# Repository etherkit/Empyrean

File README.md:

# Empyrean

### Installing Empyrean Support in Arduino IDE

1. Open the Arduino IDE and then navigate to the Preferences screen by selecting the ```File``` menu, and then ```Preferences```. Click the small button to the right of the text box labeled ```Additional Boards Manager URLs```, and then paste the following URL into the windows which pops up:
[https://github.com/etherkit/ArduinoBoards/raw/master/package_etherkit_index.json](https://github.com/etherkit/ArduinoBoards/raw/master/package_etherkit_index.json)
<br>Click OK to close this window, and then OK to close the Preferences.
2. Navigate to the Arduino Boards Manager in the IDE by selecting the ```Tools``` menu, then ```Board```, and then ```Boards Manager...```. In the search box in the upper right of the Boards Manager windows, type ```SAMD```.
3. In the search results list below, find the entry for ```Arduino SAMD Boards```, select it with your mouse, and then click the install button.
4. Next, find the entry for ```Etherkit SAMD Boards```, select it, and click the install button. Close the Boards Manager window when this is complete.
5. In the ```Tools > Boards``` menu, you should now see Empyrean Alpha and Empyrean Beta listed as board options. Select the appropriate board in order to start uploading sketches to your Empyrean.

### USB-UART (CDC) and Other Serial
You can access the built-in USB-UART (virtual serial port) by using the ```SerialUSB``` object in your sketch, just as you use ```Serial``` in AVR-powered Arduinos. You can also use pins 0 and 1 of Empyrean as a hardware serial port with the ```Serial1``` object.

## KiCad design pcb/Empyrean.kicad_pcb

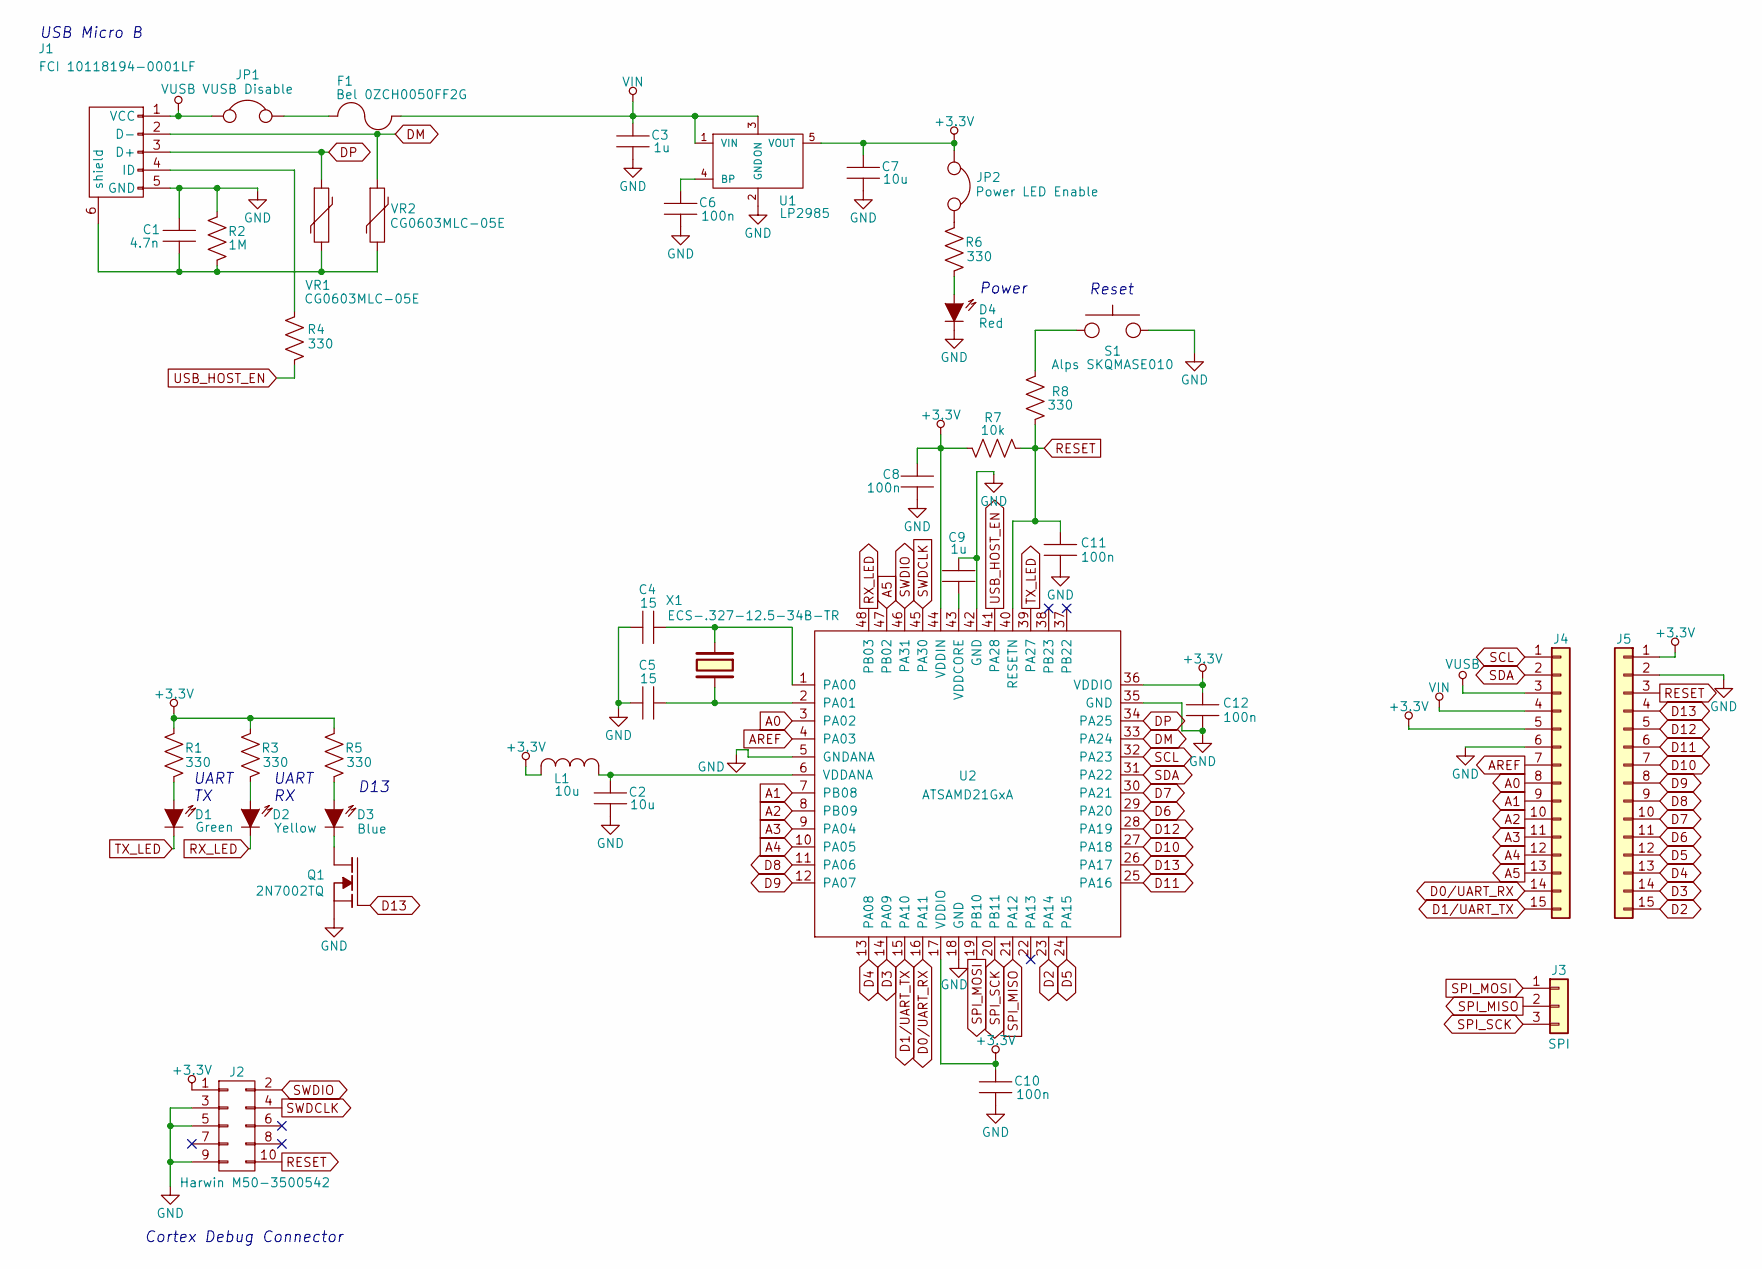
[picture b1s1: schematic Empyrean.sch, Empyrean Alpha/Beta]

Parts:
C1: 4.7n; C_0603; MPN CC0603KRX7R9BB472
C2, C7: 10u; C_0603; MPN CC0603MRX5R5BB106
C3, C9: 1u; C_0603; MPN CC0603KRX5R8BB105
C4, C5: 15; C_0603; MPN GCM1885C1H150JA16D
C6, C8, C10, C11, C12: 100n; C_0603; MPN CC0603KRX7R9BB104
D1: Green; Lite-On_LTST-C170; MPN LTST-C170KGKT
D2: Yellow; Lite-On_LTST-C170; MPN LTST-C170KSKT
D3: Blue; Lite-On_LTST-C170; MPN LTST-C170TBKT
D4: Red; Lite-On_LTST-C170; MPN LTST-C170KRKT
F1: Bel 0ZCH0050FF2G; R_1210; MPN 0ZCH0050FF2G
J1: FCI 10118194-0001LF; FCI_10118194-0001LF; MPN 10118194-0001LF
J2: Harwin M50-3500542; Harwin_M50-3500542
J3: SPI; Pin_Header_Straight_1x03_NoBorder
J4, J5: CONN_01X15; Pin_Header_Straight_1x15_NoBorder
JP1: VUSB Disable; SOLDER_JUMPER_NC
JP2: Power LED Enable; SOLDER_JUMPER_NC
L1: 10u; R_0603; MPN MLF1608E100JT000
Q1: 2N7002TQ; SOT523; MPN 2N7002TQ-7-F
R1, R3, R4, R5, R6, R8: 330; R_0603; MPN RC0603FR-07330RL
R2: 1M; R_0603; MPN RC0603FR-071ML
R7: 10k; R_0603; MPN RC0603JR-0710KL
S1: Alps SKQMASE010; Alps_SKQMASE010; MPN SKQMASE010
U1: LP2985; SOT23-5; MPN LP2985-33DBVR
U2: ATSAMD21GxA; TQFP-48_7x7mm_Pitch0.5mm; MPN ATSAMD21G18A-AUT
VR1, VR2: CG0603MLC-05E; R_0603; MPN CG0603MLC-05E
X1: ECS-.327-12.5-34B-TR; ECS_ECS-.327-12.5-34B-TR; MPN ECS-.327-12.534B-TR

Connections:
+3.3V: C7.1, C8.1, C10.1, C12.1, J2.1, J4.5, J5.1, JP2.1, L1.1, R1.1, R3.1, R5.1, R7.1, U1.5 (VOUT), U2.17 (VDDIO), U2.36 (VDDIO), U2.44 (VDDIN)
A0: J4.8, U2.3 (PA02)
A1: J4.9, U2.7 (PB08)
A2: J4.10, U2.8 (PB09)
A3: J4.11, U2.9 (PA04)
A4: J4.12, U2.10 (PA05)
A5: J4.13, U2.47 (PB02)
AREF: J4.7, U2.4 (PA03)
D0/UART_RX: J4.14, U2.16 (PA11)
D1/UART_TX: J4.15, U2.15 (PA10)
D2: J5.15, U2.23 (PA14)
D3: J5.14, U2.14 (PA09)
D4: J5.13, U2.13 (PA08)
D5: J5.12, U2.24 (PA15)
D6: J5.11, U2.29 (PA20)
D7: J5.10, U2.30 (PA21)
D8: J5.9, U2.11 (PA06)
D9: J5.8, U2.12 (PA07)
D10: J5.7, U2.27 (PA18)
D11: J5.6, U2.25 (PA16)
D12: J5.5, U2.28 (PA19)
D13: J5.4, Q1.2 (G), U2.26 (PA17)
DM: J1.2 (D-), U2.33 (PA24), VR2.1
DP: J1.3 (D+), U2.34 (PA25), VR1.1
GND: C1.1, C2.2, C3.2, C4.2, C5.2, C6.2, C7.2, C8.2, C9.1, C10.2, C11.2, C12.2, D4.2 (K), J1.5 (GND), J2.3, J2.5, J2.9, J4.6, J5.2, Q1.1 (S), R2.1, S1.2, U1.2 (GND), U2.5 (GNDANA), U2.18 (GND), U2.35 (GND), U2.42 (GND)
unnamed: C1.2, J1.6 (shield), R2.2, VR1.2, VR2.2
unnamed: C2.1, L1.2, U2.6 (VDDANA)
unnamed: C4.1, U2.1 (PA00), X1.1
unnamed: C5.1, U2.2 (PA01), X1.2
unnamed: C6.1, U1.4 (BP)
unnamed: C9.2, U2.43 (VDDCORE)
unnamed: D1.1 (A), R1.2
unnamed: D2.1 (A), R3.2
unnamed: D3.1 (A), R5.2
unnamed: D3.2 (K), Q1.3 (D)
unnamed: D4.1 (A), R6.2
unnamed: F1.1, JP1.2
unnamed: J1.4 (ID), R4.2
unnamed: JP2.2, R6.1
unnamed: R8.1, S1.1
RESET: C11.1, J2.10, J5.3, R7.2, R8.2, U2.40 (RESETN)
RX_LED: D2.2 (K), U2.48 (PB03)
SCL: J4.1, U2.32 (PA23)
SDA: J4.2, U2.31 (PA22)
SPI_MISO: J3.2, U2.21 (PA12)
SPI_MOSI: J3.1, U2.19 (PB10)
SPI_SCK: J3.3, U2.20 (PB11)
SWDCLK: J2.4, U2.45 (PA30)
SWDIO: J2.2, U2.46 (PA31)
TX_LED: D1.2 (K), U2.39 (PA27)
USB_HOST_EN: R4.1, U2.41 (PA28)
VIN: C3.1, F1.2, J4.4, U1.1 (VIN), U1.3 (ON)
VUSB: J1.1 (VCC), J4.3, JP1.1

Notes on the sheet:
Reset
Cortex Debug Connector
USB Micro B
Power
UART TX
UART RX
D13

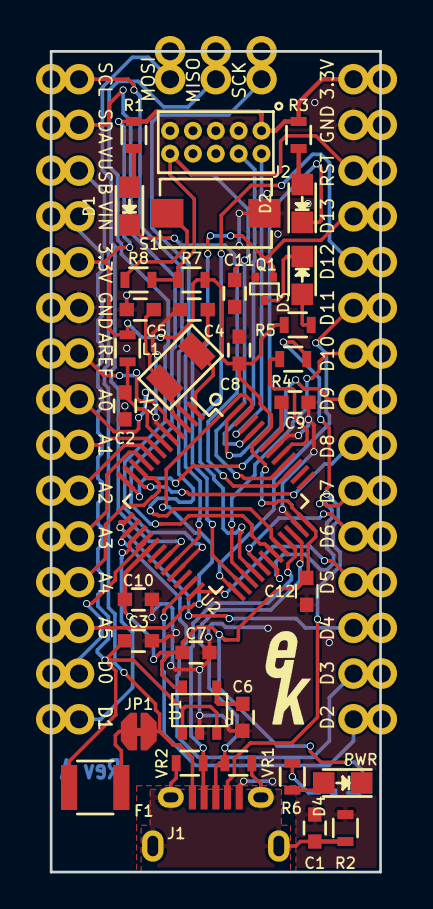
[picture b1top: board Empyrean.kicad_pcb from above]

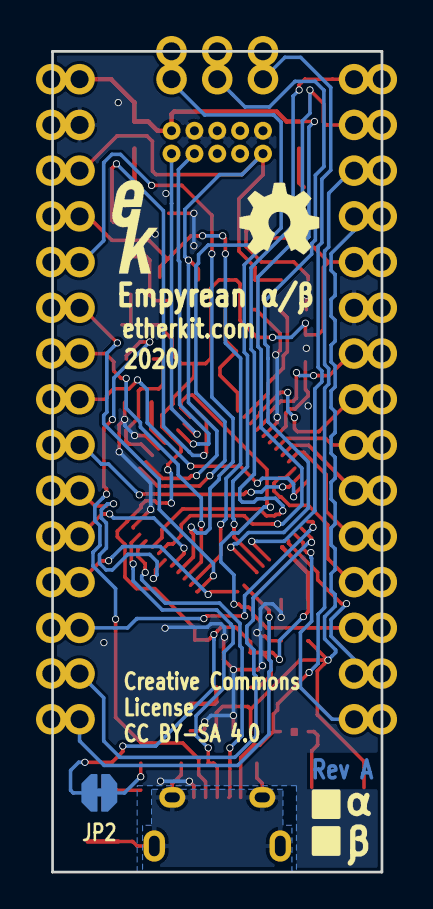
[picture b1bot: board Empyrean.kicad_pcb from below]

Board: 2 copper layers, 18.3 x 45.6 mm, 42 parts (2 on the bottom side), 53 nets.

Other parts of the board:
Ref**: Val**; EtherkitLogoSmall
Ref**#2: Val**; EtherkitLogoSmall

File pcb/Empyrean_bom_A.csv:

Component,Description,Part,References,Value,Footprint,Quantity Per PCB,Datasheet
1,,C,C6 C8 C10 C11 C12,100n,C_0603,5,
2,,C,C2 C7,10u,C_0603,2,
3,,C,C4 C5,15,C_0603,2,
4,,C,C3 C9,1u,C_0603,2,
5,,C,C1,4.7n,C_0603,1,
6,,LED,D3,Blue,Lite-On_LTST-C170,1,
7,,LED,D4,Green,Lite-On_LTST-C170,1,
8,,LED,D1,Red,Lite-On_LTST-C170,1,
9,,LED,D2,Yellow,Lite-On_LTST-C170,1,
10,,FUSE,F1,Bel 0ZCH0050FF2G,R_1210,1,
11,,CONN_01X15,J4 J5,CONN_01X15,Pin_Header_Straight_1x15_NoBorder,2,
12,,USB_OTG,J1,FCI 10118194-0001LF,FCI_10118194-0001LF,1,
13,,CONN_02X05,J2,Harwin M50-3500542,Harwin_M50-3500542,1,
14,,CONN_01X03,J3,SPI,Pin_Header_Straight_1x03_NoBorder,1,
15,,JUMPER,JP1,Power LED Enable,SOLDER_JUMPER,1,
16,,L,L1,10u,R_0603,1,
17,,MOS_N,Q1 Q4,DMG1012UW-7,SOT523,2,
18,,MOS_P,Q2 Q3,DMG1013T-7,SOT523,2,
19,,R,R5 R7 R8,100k,R_0603,3,
20,,R,R10,10k,R_0603,1,
21,,R,R2,1M,R_0603,1,
22,,R,R1 R3 R4 R6 R9 R11,330,R_0603,6,
23,,PUSHBUTTON,S1,Alps SKQMASE010,Alps_SKQMASE010,1,
24,,ATSAMD21G18A,U2,ATSAMD21GxA,TQFP-48_7x7mm_Pitch0.5mm,1,DOCUMENTATION
25,,LP2985,U1,LP2985,SOT23-5,1,
26,,VR,VR1 VR2,CG0603MLC-05E,R_0603,2,
27,,CRYSTAL,X1,ECS-.327-12.5-34B-TR,ECS_ECS-.327-12.5-34B-TR,1,





Component Groups:,27
Component Count:,45
Fitted Components:,45
Number of PCBs:,1
Total components:,45
Schematic Version:,A
Schematic Date:,2017-03-04
BoM Date:,Tue 18 Sep 2018 02:25:04 PM PDT
Schematic Source:,/home/jason/Nextcloud/Etherkit/git/Empyrean/pcb/Empyrean.sch
KiCad Version:,Eeschema 5.0.0-fee4fd1~66~ubuntu18.04.1

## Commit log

2017-03-05 Generate gerbers
2017-03-06 Export IDFv3 format
2018-03-01 Add basic board support instructions to README
2018-03-01 Fix README typo
2018-03-10 Add info about SerialUSB to README
2018-09-18 Add csv BOM
2018-11-28 Update schematic to Rev B
2019-09-17 Create LICENSE
2019-09-17 Updated PCB with castellation
2019-09-17 Add uf2 dependency
2020-06-07 Add Empyrean Quick Reference
2020-06-07 Fix alpha channel in quick ref
2020-07-22 Set proper rev on documentation
2020-07-22 Add FadeZero.ino example
2020-07-22 Add FadeEmpyrean.ino example

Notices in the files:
pcb/Empyrean.kicad_pcb:
Creative Commons CC-BY-SA
License
CC BY-SA 4.0
pcb/Empyrean.sch:
Creative Commons CC-BY_SA 4.0
